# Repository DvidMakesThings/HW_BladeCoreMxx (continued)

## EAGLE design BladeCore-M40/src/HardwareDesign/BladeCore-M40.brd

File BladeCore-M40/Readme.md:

# BladeCore-M40

BladeCore-M40 is a versatile 6-layer embedded system module built around the RP2040 microcontroller, designed for modularity and high-speed experimentation in constrained spaces.  
It uses an M.2 form factor and includes a carefully routed, length-matched 16MB QSPI flash capable of operating at full 133 MHz quad I/O speeds — theoretically up to 532 Mbps effective throughput.  

The module provides optional breakouts for ADC, I²C, UART, GPIO, and USB signals — configurable based on application needs. Core voltage is externally adjustable via a trimpot-controlled LDO (AP7335-WG-7), enabling safe overclocking without risk of oversupply.  

USB routing is dynamically switchable using the PI3USB102J, allowing the single USB-C port to connect either to the MCU or to an FT232RNQ interface for debug automation.  
Boot/reset are handled programmatically; no physical boot/reset buttons are needed.  

It also includes:
- a high-precision 3.0 V analog reference supply (AVDD),
- a unique-ID EEPROM for per-module identification,
- and default configurations that favor RP2040-based development while leaving everything else adaptable.

BladeCore-M40 is not locked into any specific use case — it is meant to be reconfigured as needed.

---

## Highlights

- **RP2040 MCU** with external core voltage supply (AP7335-WG-7) for **safe overclocking** via trimpot  
- **16MB W25Q128JV QSPI Flash**, length-matched for up to **133 MHz quad I/O** (532 Mbps effective transfer rate)  
- **PI3USB102J USB switch**: 1 USB-C can switch between MCU and FT232RNQ (auto-debug, single cable)  
- Optional ADC, I²C, UART, and GPIO breakouts — **use what you need**  
- **No physical reset/boot buttons** — fully controllable by firmware  
- **3.0 V precision AVDD** generator for analog use  
- **External EEPROM with unique ID**  
- **Custom 6-layer JLC stackup**, tuned for signal integrity  
- **DMT signature layout** with aggressive routing and style

---

## Stackup

**JLC06081H-2116 (Finished Thickness: ~0.83 mm ±0.10 mm) – 6 Layers**

- Total Layers: 6  
- Finished Thickness: ~0.83 mm (±0.10 mm)  
- Outer Copper Weight: 1 oz  
- Inner Copper Weight: 0.5 oz  
- Prepreg & Core Materials: FR4 (JLC06081H-2116)

| Layer | Description     | Material                      | Thickness (mm) |
|-------|------------------|-------------------------------|----------------|
| L1    | Signal (Top)     | Outer Copper 1 oz             | 0.0350         |
|       | Prepreg          | 2116 RC54%, 4.9mil            | 0.1164         |
| L2    | Ground Plane     | Inner Copper 0.5 oz           | 0.0152         |
|       | Core             | 0.13 mm HOZ without copper    | 0.1300         |
| L3    | Power Plane      | Inner Copper 0.5 oz           | 0.0152         |
|       | Prepreg          | 7628 RC49%, 8.6mil            | 0.2028         |
| L4    | Signal           | Inner Copper 0.5 oz           | 0.0152         |
|       | Core             | 0.13 mm HOZ without copper    | 0.1300         |
| L5    | Ground Plane     | Inner Copper 0.5 oz           | 0.0152         |
|       | Prepreg          | 2116 RC54%, 4.9mil            | 0.1164         |
| L6    | Signal (Bottom)  | Outer Copper 1 oz             | 0.0350         |
|       |                  | **Total Thickness**           | **0.8304 mm**  |

---

## Pinout

| Pin | Signal      | Direction | Description |
|-----|-------------|-----------|-------------|
| 1   | GP15        | I/O       |             |
| 2   | GP29        | I/O       | ADC Channel 3 |
| 3   | GP14        | I/O       |             |
| 4   | GP28        | I/O       | ADC Channel 2 |
| 5   | GP13        | I/O       |             |
| 6   | GP27        | I/O       | ADC Channel 1 |
| 7   | GP12        | I/O       |             |
| 8   | GP26        | I/O       | ADC Channel 0 |
| 9   | GP11        | I/O       |             |
| 10  | GP25        | I/O       | USB MUX Select. For normal functionality, remove M1 and populate M3 (RP2040 USB) or M2 (FT232 USB). Default: M1 = 0Ω, M3 = 10K, M2 = DNI. |
| 11  | GP10        | I/O       |             |
| 12  | GP24        | I/O       |             |
| 13  | GP9         | I/O       | UART1 RX. Connected to FT232 via R01 (DNI). |
| 14  | GP23        | I/O       |             |
| 15  | GP8         | I/O       | UART1 TX. Connected to FT232 via T11 (DNI). |
| 16  | GP22        | I/O       |             |
| 17  | GP7         | I/O       |             |
| 18  | GP21        | I/O       |             |
| 19  | GP6         | I/O       |             |
| 20  | GP20        | I/O       |             |
| 21  | GP5         | I/O       | I2C0 SCL. Pulled high via R23 (3.3K). Remove R3 (0Ω) for non-I2C use. |
| 22  | GP19        | I/O       |             |
| 23  | GP4         | I/O       | I2C0 SDA. Pulled high via R24 (3.3K). Remove R4 (0Ω) for non-I2C use. |
| 24  | GP18        | I/O       |             |
| 25  | GP3         | I/O       |             |
| 26  | GP17        | I/O       |             |
| 27  | GP2         | I/O       |             |
| 28  | GP16        | I/O       |             |
| 29  | GP1         | I/O       | UART0 RX. Connected to FT232 via M1 (0Ω). |
| 30  | GND         | —         |             |
| 31  | GP0         | I/O       | UART0 TX. Connected to FT232 via T01 (0Ω). |
| 32  | NC          | —         | No functionality, used by BladeCore-M54. |
| 33  | GND         | —         |             |
| 34  | NC          | —         | No functionality, used by BladeCore-M54. |
| 35  | NC          | —         | No functionality, used by BladeCore-M54. |
| 36  | NC          | —         | No functionality, used by BladeCore-M54. |
| 37  | NC          | —         | No functionality, used by BladeCore-M54. |
| 38  | NC          | —         | No functionality, used by BladeCore-M54. |
| 39  | NC          | —         | No functionality, used by BladeCore-M54. |
| 40  | NC          | —         | No functionality, used by BladeCore-M54. |
| 41  | NC          | —         | No functionality, used by BladeCore-M54. |
| 42  | NC          | —         | No functionality, used by BladeCore-M54. |
| 43  | NC          | —         | No functionality, used by BladeCore-M54. |
| 44  | NC          | —         | No functionality, used by BladeCore-M54. |
| 45  | NC          | —         | No functionality, used by BladeCore-M54. |
| 46  | NC          | —         | No functionality, used by BladeCore-M54. |
| 47  | NC          | —         | No functionality, used by BladeCore-M54. |
| 48  | NC          | —         | No functionality, used by BladeCore-M54. |
| 49  | NC          | —         | No functionality, used by BladeCore-M54. |
| 50  | NC          | —         | No functionality, used by BladeCore-M54. |
| 51  | GND         | —         | System ground |
| 52  | GND         | —         | System ground |
| 53  | USB D+      | I/O       |             |
| 54  | RESET       | Input     |             |
| 55  | USB D-      | I/O       |             |
| 56  | SWDIO       | I/O       |             |
| 57  | DETECT      | -         | Pull low externally |
| 58  | SWCLK       | Input     |             |
| 67  | +3.3V       | PWR       | RP2040 supply voltage. Max 3.6V, typical 3.3V. |
| 68  | +3.3V       | PWR       |             |
| 69  | +3.3V       | PWR       |             |
| 70  | GND         | —         | System ground |
| 71  | GND         | —         | System ground |
| 72  | GND         | —         | System ground |
| 73  | VBUS        | PWR IN    | External power input. Max 5.5V. |
| 74  | VBUS        | PWR IN    | External power input. Max 5.5V. |
| 75  | VBUS        | PWR IN    | External power input. Max 5.5V. |

## Misc: Core Voltage & Overclocking

To overclock the MCU, it's possible to supply more than 1.1 V to the core.  
By default, **external core voltage generation** is enabled using the **AP7335-WG-7**, which is activated via **J1**.  
The output voltage is set by adjusting the **R1 trimpot**.

> ⚠️ It is safe — the voltage range is limited by design and cannot damage the MCU.

### Voltage Range (Set by Divider)

| R1 (Trimpot) | Total Resistance (R28 + R1) | VOUT (approx) |
|--------------|----------------------------|----------------|
| 25 kΩ (max)  | 47 kΩ                       | 1.02 V         |
| 12.5 kΩ      | 34.5 kΩ                     | 1.14 V         |
| 0 Ω (min)    | 22 kΩ                       | 1.22 V         |

### Use Cases

- **Low Power Mode:** R1 = 25 kΩ → ~1.02 V  
- **Default / Safe:** R1 = 12.5 kΩ → ~1.14 V  
- **High Performance / Overclocking:** R1 = 0 Ω → ~1.22 V  

### VOUT Behavior Across Temperatures and Trim Settings

The AP7335-WG-7 regulator is affected by temperature-dependent reference voltage (VREF), output voltage accuracy, and resistor tolerances.  
This section outlines the **worst-case VOUT values** at cold, normal, and hot temperatures, across all trimpot settings.

> ⚙️ **Calculation Parameters:**
> - VOUT Accuracy: ±2% (from AP7335-WG-7 datasheet)
> - VREF Variation: Based on VREF vs. Temperature graph  
>   - −50 °C → 0.89 V  
>   - 25 °C → 0.80 V  
>   - 125 °C → 0.782 V
> - Resistors used: 1% tolerance (R27 = 12 kΩ, R28 = 22 kΩ, R1 = 0–25 kΩ trimpot)

The RP2040's **absolute maximum core voltage is 1.3 V** — values exceeding this may cause damage.

---

### ❄️ Cold (–50 °C, VREF = 0.89 V)

**Max Trim (R1 = 25 kΩ, Rb = 47 kΩ)**  
VOUT: **1.090 V – 1.144 V** ✅ Safe

**Mid Trim (R1 = 12.5 kΩ, Rb = 34.5 kΩ)**  
VOUT: **1.170 V – 1.230 V** ✅ Safe

**Min Trim (R1 = 0 Ω, Rb = 22 kΩ)**  
VOUT: **1.339 V – 1.413 V** ❌ Danger – exceeds RP2040 1.3 V limit

---

### 🌤️ Normal (25 °C, VREF = 0.80 V)

**Max Trim (R1 = 25 kΩ, Rb = 47 kΩ)**  
VOUT: **0.980 V – 1.029 V** ✅ Safe

**Mid Trim (R1 = 12.5 kΩ, Rb = 34.5 kΩ)**  
VOUT: **1.051 V – 1.106 V** ✅ Safe

**Min Trim (R1 = 0 Ω, Rb = 22 kΩ)**  
VOUT: **1.201 V – 1.265 V** ✅ Safe

---

### 🔥 Hot (125 °C, VREF = 0.782 V)

**Max Trim (R1 = 25 kΩ, Rb = 47 kΩ)**  
VOUT: **0.958 V – 1.005 V** ✅ Safe

**Mid Trim (R1 = 12.5 kΩ, Rb = 34.5 kΩ)**  
VOUT: **1.028 V – 1.082 V** ✅ Safe

**Min Trim (R1 = 0 Ω, Rb = 22 kΩ)**  
VOUT: **1.180 V – 1.243 V** ✅ Safe

### Switching to Internal Core LDO

To use the **internally generated core voltage** (from RP2040's internal LDO):

1. Move **J1 → J2**  
2. Populate **J3** with a 0 Ω jumper  

**Default configuration:**
- J1 = 10 kΩ  
- J2 = DNI  
- J3 = DNI

---
## License
This project is licensed under the GPL-3.0 License. See the [LICENSE](LICENSE) file for details.

## Contact
For questions or feedback:
- Email: [dvidmakesthing@gmail.com](mailto:dvidmakesthing@gmail.com)
- GitHub: [DvidMakesThings](https://github.com/DvidMakesThings)

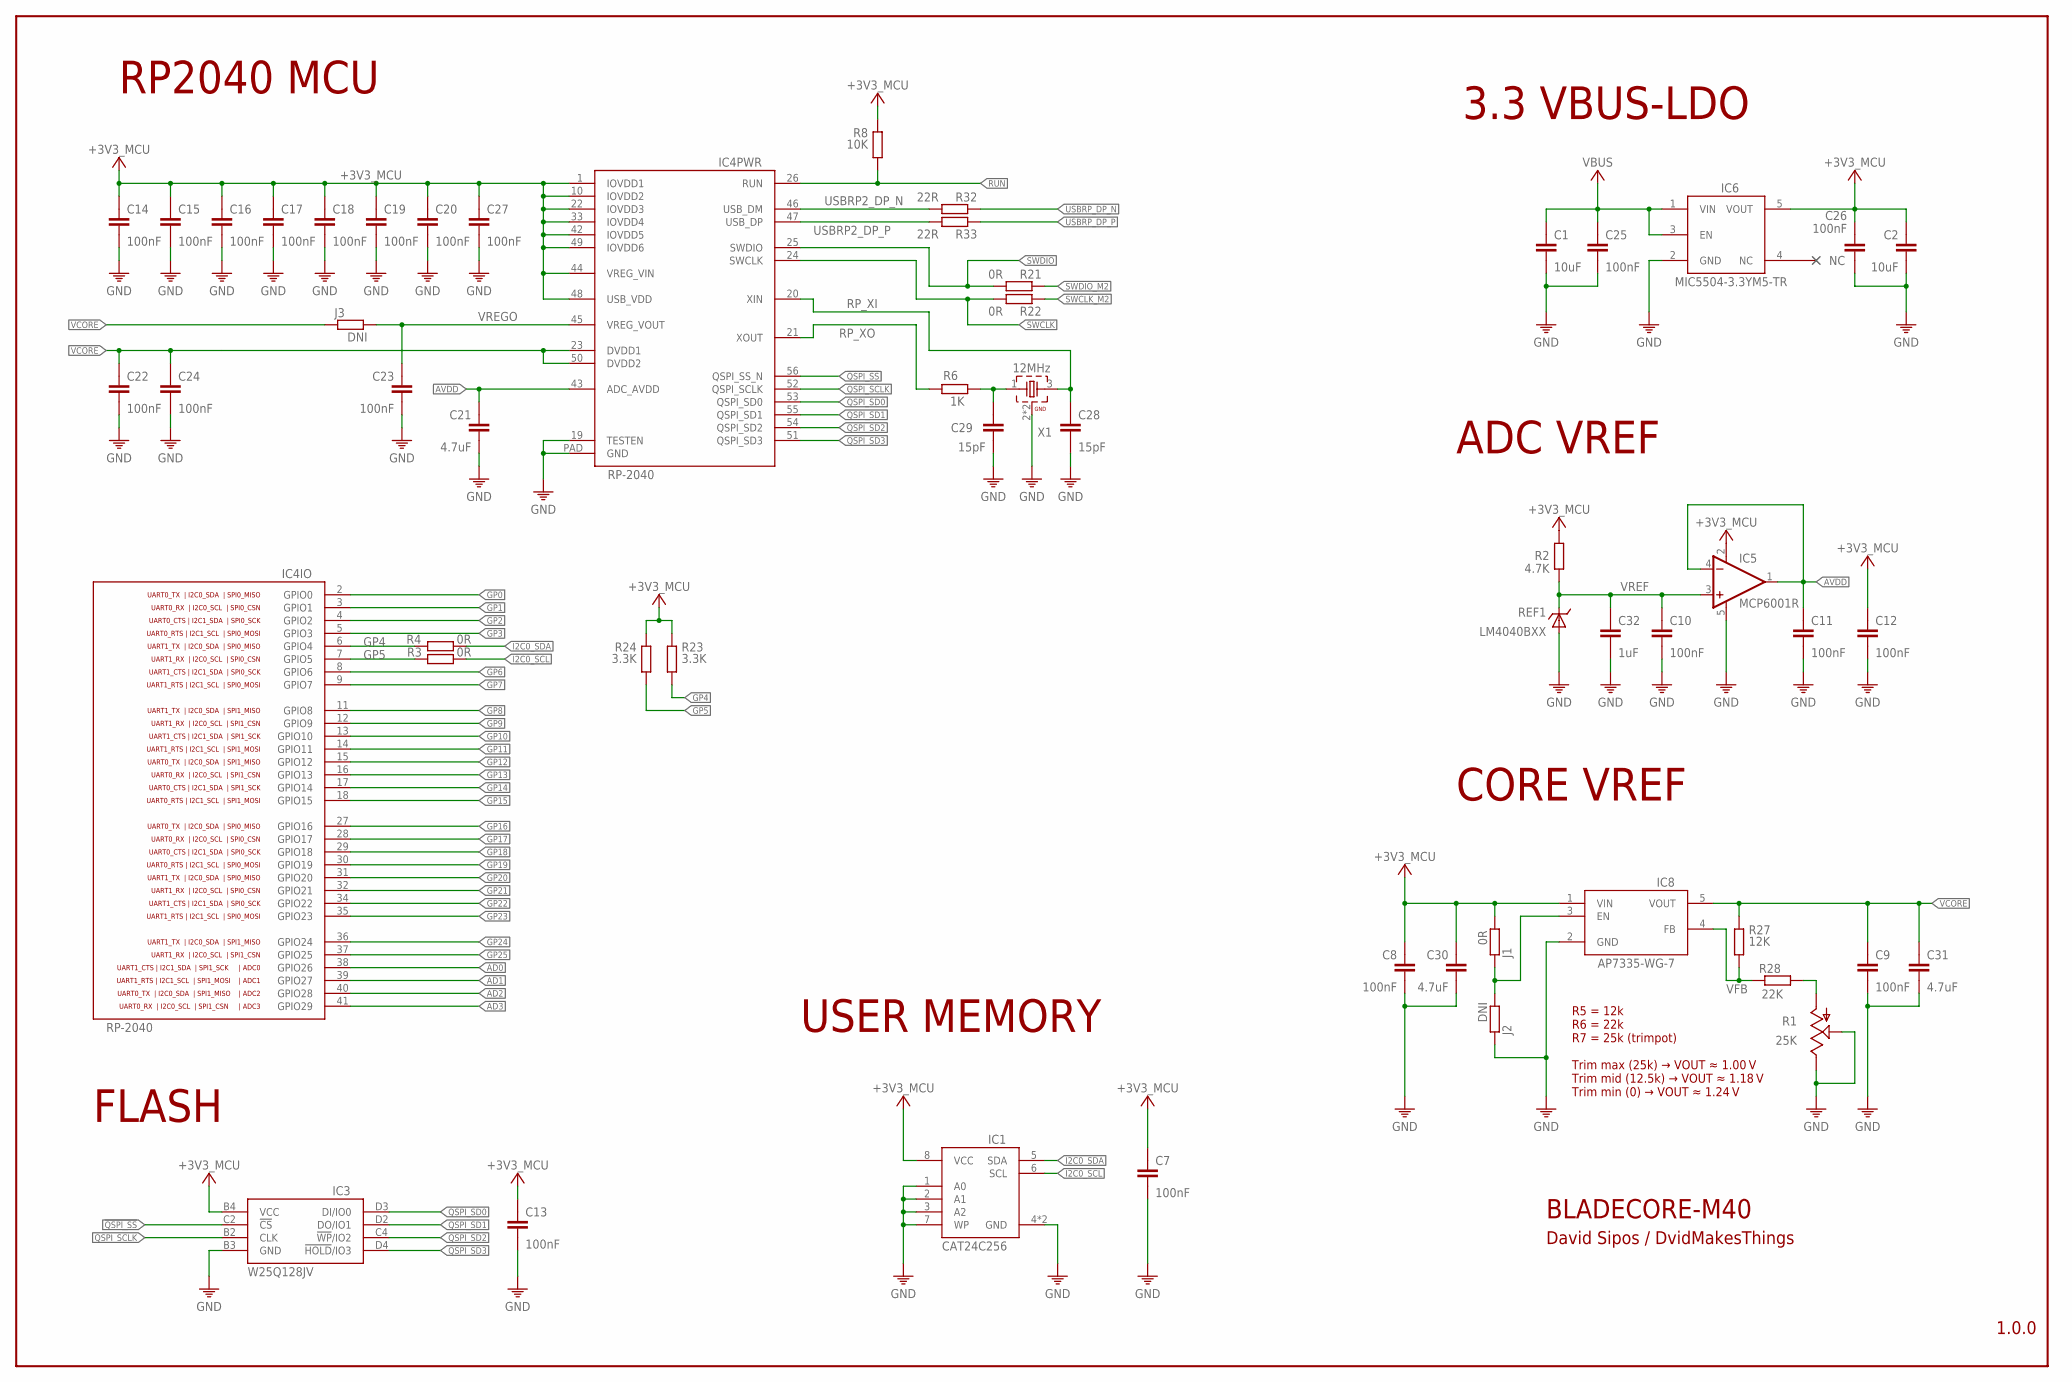
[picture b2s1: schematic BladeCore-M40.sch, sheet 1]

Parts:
C1, C2: 10uF; 0805
C7, C8, C9, C10, C11, C12, C13, C14, C15, C16, C17, C18, C19, C20, C22, C23, C24, C25, C26, C27: 100nF; 0201
C21, C30, C31: 4.7uF; C0402
C28, C29: 15pF; 0201
C32: 1uF; C0402
IC1: CAT24C512HU5IGT3; SON50P300X200X50-9T130X140N
IC3: W25Q128JVCIQ TR; BGA24C100P4X6_800X600X120N
IC4: RP-2040; QFN56
IC5: MCP6001R; SOT23-5
IC6: MIC5504-3.3YM5-TR; SOT23-5
IC8: AP7335-WG-7; SOT23-5
J1: 0R; R0201
J2, J3: DNI; R0201
R1: 25K; SMD_TRIMMER
R2: 4.7K; R0201
R3, R4, R21, R22: 0R; R0201
R6: 1K; R0201
R8: 10K; R0201
R23, R24: 3.3K; R0201
R27: 12K; R0201
R28: 22K; R0201
R32, R33: 22R; R0201
REF1: LM4040BXX; SOT23
X1: 12MHz; WE-XTAL_CFPX-180

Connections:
!QSPI_SS: IC3.C2 (!CS), IC4.56 (QSPI_SS_N)
+3V3_MCU: C2.1, C7.1, C8.1, C12.1, C13.1, C14.1, C15.1, C16.1, C17.1, C18.1, C19.1, C20.1, C26.1, C27.1, C30.1, IC1.8 (VCC), IC3.B4 (VCC), IC4.1 (IOVDD1), IC4.10 (IOVDD2), IC4.22 (IOVDD3), IC4.33 (IOVDD4), IC4.42 (IOVDD5), IC4.44 (VREG_VIN), IC4.48 (USB_VDD), IC4.49 (IOVDD6), IC5.2 (V+), IC6.5 (VOUT), IC8.1 (VIN), J1.1, R2.2, R8.1, R23.1, R24.1; also elsewhere on the board
AD0: IC4.38 (GPIO26); also elsewhere on the board
AD1: IC4.39 (GPIO27); also elsewhere on the board
AD2: IC4.40 (GPIO28); also elsewhere on the board
AD3: IC4.41 (GPIO29); also elsewhere on the board
AVDD: C11.1, C21.1, IC4.43 (ADC_AVDD), IC5.1 (OUT), IC5.4 (-IN)
FBTRIM: R1.3, R28.2
GND: C1.2, C2.2, C7.2, C8.2, C9.2, C10.2, C11.2, C12.2, C13.2, C14.2, C15.2, C16.2, C17.2, C18.2, C19.2, C20.2, C21.2, C22.2, C23.2, C24.2, C25.2, C26.2, C27.2, C28.2, C29.2, C30.2, C31.2, C32.2, IC1.1 (A0), IC1.2 (A1), IC1.3 (A2), IC1.4 (GND), IC1.7 (WP), IC1.9 (GND), IC3.B3 (GND), IC4.19 (TESTEN), IC4.PAD (GND), IC5.5 (V-), IC6.2 (GND), IC8.2 (GND), J2.2, R1.1, R1.2, REF1.2 (A), REF1.3 (A), X1.2 (GND), X1.4 (GND); also elsewhere on the board
GP0: IC4.2 (GPIO0); also elsewhere on the board
GP1: IC4.3 (GPIO1); also elsewhere on the board
GP2: IC4.4 (GPIO2); also elsewhere on the board
GP3: IC4.5 (GPIO3); also elsewhere on the board
GP4: IC4.6 (GPIO4), R4.1, R23.2; also elsewhere on the board
GP5: IC4.7 (GPIO5), R3.1, R24.2; also elsewhere on the board
GP6: IC4.8 (GPIO6); also elsewhere on the board
GP7: IC4.9 (GPIO7); also elsewhere on the board
GP8: IC4.11 (GPIO8); also elsewhere on the board
GP9: IC4.12 (GPIO9); also elsewhere on the board
GP10: IC4.13 (GPIO10); also elsewhere on the board
GP11: IC4.14 (GPIO11); also elsewhere on the board
GP12: IC4.15 (GPIO12); also elsewhere on the board
GP13: IC4.16 (GPIO13); also elsewhere on the board
GP14: IC4.17 (GPIO14); also elsewhere on the board
GP15: IC4.18 (GPIO15); also elsewhere on the board
GP16: IC4.27 (GPIO16); also elsewhere on the board
GP17: IC4.28 (GPIO17); also elsewhere on the board
GP18: IC4.29 (GPIO18); also elsewhere on the board
GP19: IC4.30 (GPIO19); also elsewhere on the board
GP20: IC4.31 (GPIO20); also elsewhere on the board
GP21: IC4.32 (GPIO21); also elsewhere on the board
GP22: IC4.34 (GPIO22); also elsewhere on the board
GP23: IC4.35 (GPIO23); also elsewhere on the board
GP24: IC4.36 (GPIO24); also elsewhere on the board
GP25: IC4.37 (GPIO25); also elsewhere on the board
I2C0_SCL: IC1.6 (SCL), R3.2
I2C0_SDA: IC1.5 (SDA), R4.2
unnamed: IC8.3 (EN), J1.2, J2.1
unnamed: C29.1, R6.1, X1.1
QSPI_SCLK: IC3.B2 (CLK), IC4.52 (QSPI_SCLK)
QSPI_SD0: IC3.D3 (DI/IO0), IC4.53 (QSPI_SD0)
QSPI_SD1: IC3.D2 (DO/IO1), IC4.55 (QSPI_SD1)
QSPI_SD2: IC3.C4 (!WP!/IO2), IC4.54 (QSPI_SD2)
QSPI_SD3: IC3.D4 (!HOLD!/IO3), IC4.51 (QSPI_SD3)
RP_XI: C28.1, IC4.20 (XIN), X1.3 (2)
RP_XO: IC4.21 (XOUT), R6.2
RUN: IC4.26 (RUN), R8.2; also elsewhere on the board
SWCLK: IC4.24 (SWCLK), R22.2
SWCLK_M2: R22.1; also elsewhere on the board
SWDIO: IC4.25 (SWDIO), R21.2
SWDIO_M2: R21.1; also elsewhere on the board
USBRP2_DP_N: IC4.46 (USB_DM), R32.2
USBRP2_DP_P: IC4.47 (USB_DP), R33.2
USBRP_DP_N: R32.1; also elsewhere on the board
USBRP_DP_P: R33.1; also elsewhere on the board
VBUS: C1.1, C25.1, IC6.1 (VIN), IC6.3 (EN); also elsewhere on the board
VCORE: C9.1, C22.1, C24.1, C31.1, IC4.23 (DVDD1), IC4.50 (DVDD2), IC8.5 (VOUT), J3.2, R27.1
VFB: IC8.4 (FB), R27.2, R28.1
VREF: C10.1, C32.1, IC5.3 (+IN), R2.1, REF1.1 (C)
VREGO: C23.1, IC4.45 (VREG_VOUT), J3.1

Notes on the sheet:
RP2040 MCU
ADC VREF
BLADECORE-M40
1.0.0
David Sipos / DvidMakesThings
3.3 VBUS-LDO
CORE VREF
R5 = 12k R6 = 22k R7 = 25k (trimpot) Trim max (25k) → VOUT ≈ 1.00 V Trim mid (12.5k) → VOUT ≈ 1.18 V Trim min (0) → VOUT ≈ 1.24 V
FLASH
USER MEMORY

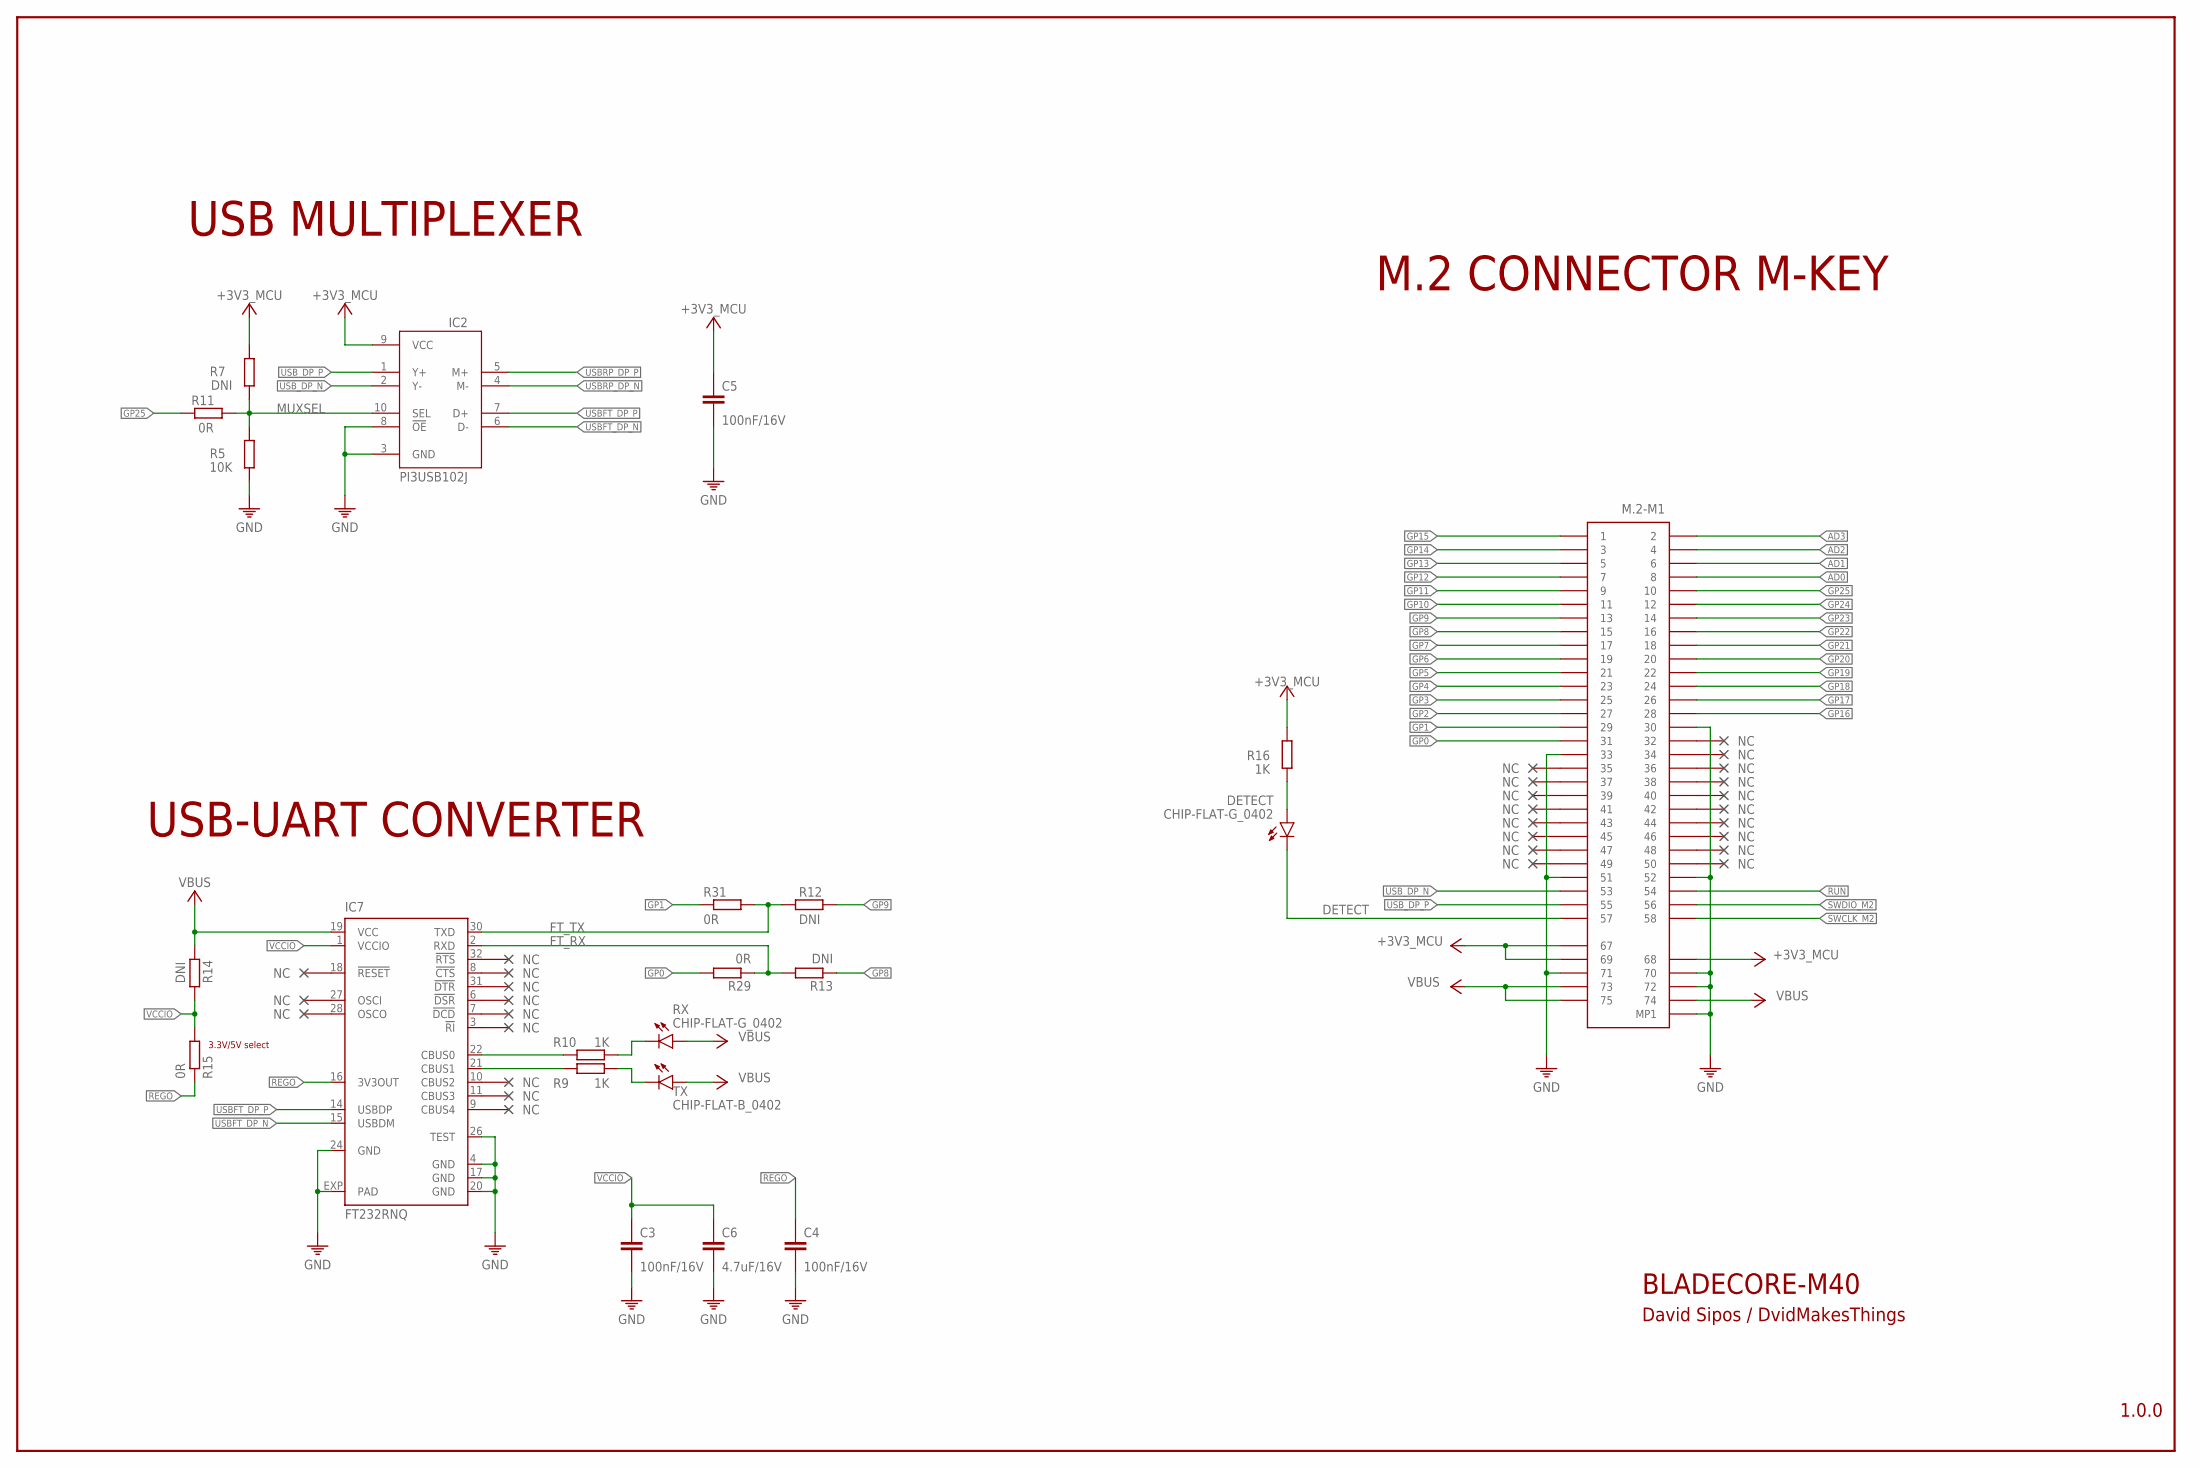
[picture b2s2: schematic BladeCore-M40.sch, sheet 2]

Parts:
C3, C4, C5: 100nF/16V; 0201
C6: 4.7uF/16V; 0201
DETECT: CHIP-FLAT-G_0402; LEDC1005X25N_FLAT-G
IC2: PI3USB102J; QFN40P120X140X35-10N
IC7: FT232RNQ; QFN32
M.2-M1: M.2-M-KEY
R5: 10K; R0201
R7, R12, R13, R14: DNI; R0201
R9, R10, R16: 1K; R0201
R11, R15, R29, R31: 0R; R0201
RX: CHIP-FLAT-G_0402; LEDC1005X25N_FLAT-G
TX: CHIP-FLAT-B_0402; LEDC1005X25N_FLAT-B

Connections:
+3V3_MCU: C5.1, IC2.9 (VCC), M.2-M1.P$67 (67), M.2-M1.P$68 (68), M.2-M1.P$69 (69), R7.2, R16.2; also elsewhere on the board
AD0: M.2-M1.P$8 (8); also elsewhere on the board
AD1: M.2-M1.P$6 (6); also elsewhere on the board
AD2: M.2-M1.P$4 (4); also elsewhere on the board
AD3: M.2-M1.P$2 (2); also elsewhere on the board
DETECT: DETECT.C, M.2-M1.P$57 (57)
FT_RX: IC7.2 (RXD), R13.2, R29.1
FT_TX: IC7.30 (TXD), R12.1, R31.2
GND: C3.2, C4.2, C5.2, C6.2, IC2.3 (GND), IC2.8 (!OE), IC7.4 (GND), IC7.17 (GND), IC7.20 (GND), IC7.24 (GND), IC7.26 (TEST), IC7.EXP (PAD), M.2-M1.MT1 (MP1), M.2-M1.P$30 (30), M.2-M1.P$33 (33), M.2-M1.P$51 (51), M.2-M1.P$52 (52), M.2-M1.P$70 (70), M.2-M1.P$71 (71), M.2-M1.P$72 (72), R5.1; also elsewhere on the board
GP0: M.2-M1.P$31 (31), R29.2; also elsewhere on the board
GP1: M.2-M1.P$29 (29), R31.1; also elsewhere on the board
GP2: M.2-M1.P$27 (27); also elsewhere on the board
GP3: M.2-M1.P$25 (25); also elsewhere on the board
GP4: M.2-M1.P$23 (23); also elsewhere on the board
GP5: M.2-M1.P$21 (21); also elsewhere on the board
GP6: M.2-M1.P$19 (19); also elsewhere on the board
GP7: M.2-M1.P$17 (17); also elsewhere on the board
GP8: M.2-M1.P$15 (15), R13.1; also elsewhere on the board
GP9: M.2-M1.P$13 (13), R12.2; also elsewhere on the board
GP10: M.2-M1.P$11 (11); also elsewhere on the board
GP11: M.2-M1.P$9 (9); also elsewhere on the board
GP12: M.2-M1.P$7 (7); also elsewhere on the board
GP13: M.2-M1.P$5 (5); also elsewhere on the board
GP14: M.2-M1.P$3 (3); also elsewhere on the board
GP15: M.2-M1.P$1 (1); also elsewhere on the board
GP16: M.2-M1.P$28 (28); also elsewhere on the board
GP17: M.2-M1.P$26 (26); also elsewhere on the board
GP18: M.2-M1.P$24 (24); also elsewhere on the board
GP19: M.2-M1.P$22 (22); also elsewhere on the board
GP20: M.2-M1.P$20 (20); also elsewhere on the board
GP21: M.2-M1.P$18 (18); also elsewhere on the board
GP22: M.2-M1.P$16 (16); also elsewhere on the board
GP23: M.2-M1.P$14 (14); also elsewhere on the board
GP24: M.2-M1.P$12 (12); also elsewhere on the board
GP25: M.2-M1.P$10 (10), R11.2; also elsewhere on the board
MUXSEL: IC2.10 (SEL), R5.2, R7.1, R11.1
unnamed: DETECT.A, R16.1
unnamed: IC7.22 (CBUS0), R10.1
unnamed: IC7.21 (CBUS1), R9.1
unnamed: R9.2, TX.C
unnamed: R10.2, RX.C
REGO: C4.1, IC7.16 (3V3OUT), R15.1
RUN: M.2-M1.P$54 (54); also elsewhere on the board
SWCLK_M2: M.2-M1.P$58 (58); also elsewhere on the board
SWDIO_M2: M.2-M1.P$56 (56); also elsewhere on the board
USBFT_DP_N: IC2.6 (D-), IC7.15 (USBDM)
USBFT_DP_P: IC2.7 (D+), IC7.14 (USBDP)
USBRP_DP_N: IC2.4 (M-); also elsewhere on the board
USBRP_DP_P: IC2.5 (M+); also elsewhere on the board
USB_DP_N: IC2.2 (Y-), M.2-M1.P$53 (53)
USB_DP_P: IC2.1 (Y+), M.2-M1.P$55 (55)
VBUS: IC7.19 (VCC), M.2-M1.P$73 (73), M.2-M1.P$74 (74), M.2-M1.P$75 (75), R14.2, RX.A, TX.A; also elsewhere on the board
VCCIO: C3.1, C6.1, IC7.1 (VCCIO), R14.1, R15.2

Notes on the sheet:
3.3V/5V select
USB MULTIPLEXER
USB-UART CONVERTER
M.2 CONNECTOR M-KEY
BLADECORE-M40
1.0.0
David Sipos / DvidMakesThings

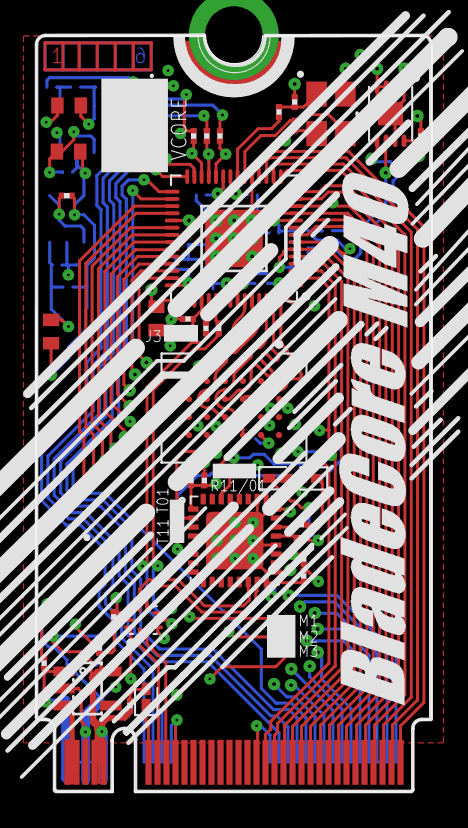
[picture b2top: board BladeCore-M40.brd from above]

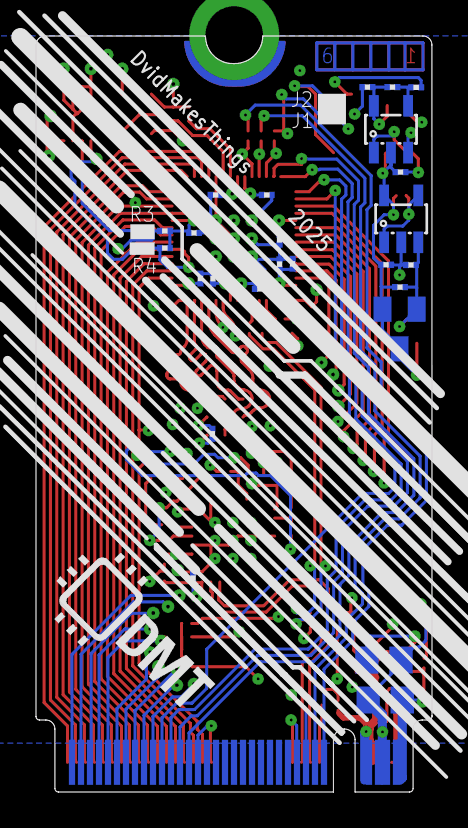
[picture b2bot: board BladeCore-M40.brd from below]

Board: 6 copper layers, 22.0 x 42.0 mm, 76 parts (31 on the bottom side), 75 nets.

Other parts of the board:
U$1: DMT

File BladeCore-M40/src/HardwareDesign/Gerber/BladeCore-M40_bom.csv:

Comment,Designator,Footprint,LCSC Part #
,M.2-M1,M.2-M-KEY,
0R,R11 R15 R21 R22 R29 R31,R0201,
1K,R6 R9 R10 R16,R0201,
1uF,C32,C0402,
4.7uF,C21 C30 C31,C0402,
4.7uF/16V,C6,0201,
10K,R5 R8,R0201,
12MHz,X1,WE-XTAL_CFPX-180,
15pF,C28 C29,0201,
22R,R32 R33,R0201,
25K,R1,SMD_TRIMMER,
100nF,C7 C11 C23 C25 C26,0201,
100nF/16V,C3 C5,0201,
CAT24C512HU5IGT3,IC1,SON50P300X200X50-9T130X140N,
CHIP-FLAT-B_0402,TX,LEDC1005X25N_FLAT-B,
CHIP-FLAT-G_0402,DETECT RX,LEDC1005X25N_FLAT-G,
DNI,R7 R12 R13 R14 R30,R0201,
FT232RNQ,IC7,QFN32,
MIC5504-3.3YM5-TR,IC6,SOT23-5,
PI3USB102J,IC2,QFN40P120X140X35-10N,
RP-2040,IC4,QFN56,
W25Q128JVCIQ TR,IC3,BGA24C100P4X6_800X600X120N,
,M.2-M1,M.2-M-KEY,
0R,R3 R4 R17,R0201,
3.3K,R23 R24,R0201,
4.7K,R2,R0201,
10uF,C1 C2,0805,
12K,R27,R0201,
22K,R28,R0201,
100nF,C8 C9 C10 C12 C13 C14 C15 C16 C17 C18 C19 C20 C22 C24 C27,0201,
100nF/16V,C4,0201,
AP7335-WG-7,IC8,SOT23-5,
DNI,R18,R0201,
LM4040BXX,REF1,SOT23,
MCP6001R,IC5,SOT23-5,

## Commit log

2025-05-16 M40 design files
2025-05-29 Finish M40 design
2025-05-30 update gerbers
2025-06-02 Start with M54
